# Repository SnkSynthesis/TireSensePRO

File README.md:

# TireSensePRO

Repository for Team 6's Tire Pressure and Temperature Monitoring System: TireSensePRO

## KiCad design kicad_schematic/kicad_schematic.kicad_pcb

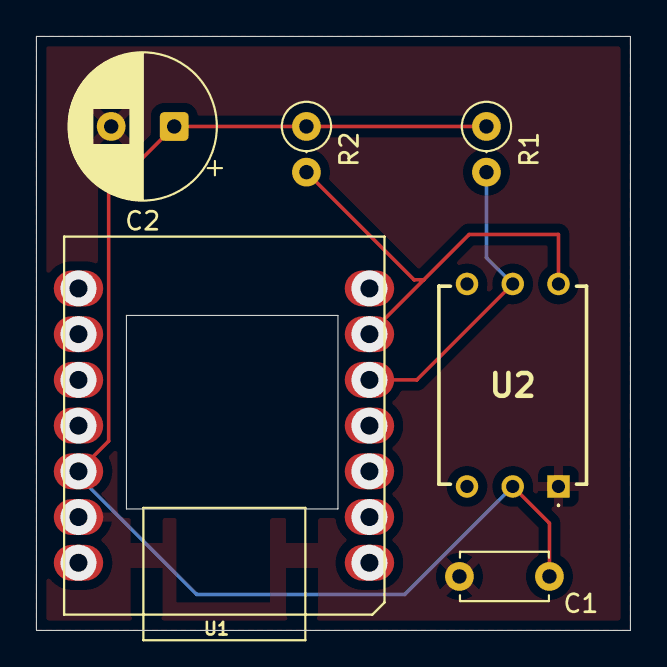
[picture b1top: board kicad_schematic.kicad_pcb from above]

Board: 2 copper layers, 33.0 x 33.0 mm, 6 parts (0 on the bottom side), 4 nets.

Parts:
C1: 100n; C_Disc_D4.7mm_W2.5mm_P5.00mm
C2: 100u; CP_Radial_D8.0mm_P3.50mm
R1, R2: 10k; R_Axial_DIN0207_L6.3mm_D2.5mm_P2.54mm_Vertical
U1: XIAO-ESP32C3; MOUDLE14P-SMD-2.54-21X17.8MM
U2: ABP2DANT100PG2A3XX

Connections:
+3V3: C1.1, C2.1, R1.1, R2.1, U1.12 (3V3), U2.2 (VDD)
GND: C1.2, C2.2, U1.13 (GND), U2.1 (GND)
unnamed: R1.2, U1.5 (PA8_A4_D4_SDA), U2.5 (SDA)
unnamed: R2.2, U1.6 (PA9_A5_D5_SCL), U2.6 (SCL)

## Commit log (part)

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2026-01-14 Create an initial schematic for pressue sensor
2026-01-18 Complete initial schematic
2026-01-19 Add schematic screenshot to README.md
2026-01-19 Fix image syntax in README.md
2026-01-25 Finish PCB, update schematic, and upload CAD folders from xiao/pressure sensor
2026-01-26 Write pressure sensor code
2026-01-28 Add ground plane and gerber files
2026-02-08 Create ADS1115 Code for 4 Input
2026-02-17 Refactor pressure sensor code into a class
2026-02-18 Update gerber files
2026-02-22 Update ADS1115 code to compute temperature C
2026-03-04 Committing Receiver Code
    Implements the ESP-NOW master receiver that collects data packets from all sensor nodes. The master can also send commands back to nodes to switch between operating modes (e.g., Park mode for low-pow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
    The implementation was developed using a combination of official documentation, tutorials, AI assistance, and original code written for this project.
2026-03-04 Create node_sender
2026-03-04 Committing node transmitter code
    Transmitter code for node 1 (all the other nodes have the same code, NODE_ID (1 - 4) is the only difference btwn them)
    Uses ESP-NOW protocol, when changing receiver, need to MATCH master MAC address Sends pressure and temp data received from pressure sensor. Accepts mode, park or race back from master (receiver), if 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
    This code was developed using a combination of official documentation, tutorials, AI assistance, and original code written for this project.
2026-03-04 MAC Address Code
    Code to get the MAC address (prints MAC Address to serial)
2026-03-04 add screen code
2026-03-04 Modify ADC code
2026-03-04 Add voltage to ADC code serial output
2026-03-08 Delete src/screen_code directory
    this was the crap from the previous screen
2026-03-08 test code for screen display
2026-03-09 initial version of the integrated code. IR sensor input not yet included
2026-03-09 updated to include R/P mode symbol and use a button to switch between modes
2026-03-11 display_receiver_test
    Test code
